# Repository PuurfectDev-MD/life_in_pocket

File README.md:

# Life in Pocket

This is a self-claimed cutesy 😛, portable, all-in-one journalling device for you to keep track of your life moments and memories through images taken through the inbuilt camera and voice recording taken through the inbuilt microphone. You can save memories with a title, detailed description and multiple pictures to enrich your journal timeline thorugh the means of an api to the website [Keep](https://keeplife.vercel.app/).

Create an account at [Keep](https://keeplife.vercel.app/) and begin Keep-ing :)

---

# Why build life_in_pocket?
I have always feared that life will just slip by while I am on autopilot. To tackle that fear I have always been keen on journalling and capturing moments to reminisce later. Building Keep and life_in_pocket has allowed me to do exactly that, capture life! I built this in the hopes of solving that fear/FOMO for me and potentially for others. 

---

## Custom build 3d Case

## Single board 2 layer PCB

# Features

**Capture Moments** — With the ondevice camera take pcitures and videos and save to sd card or/and upload to your keep account.

**Record Voice** — Record and reflect on your day, feelings and mood from the ondevice inp441 mic module to save to SD card or your Keep account.

**GUI on the TFT** — 2inch bright color tft screen where you can fetch your timeline straight from your keep account to view it ondevice without any phone or computer.

 See [Keep](https://github.com/PuurfectDev-MD/keep) for more details on the API and account.

---

# Project Structure
### 3D Case Assets
| Path / File | Description | Notes |
| :--- | :--- | :--- |
| **[3D Models](./3d%20models/)** | Root directory for all CAD data | — |
| `↳ /Fusion 360` | Original source files for the case design | — |
| `  ↳ assembly.f3d` | Master file with front/backplates & holes | **Use for printing** |
| `  ↳ frontplate.f3d` | Individual front component | Import file |
| `  ↳ backplate.f3d` | Individual back component | Import file |
| `  ↳ STEP files` | Standardized CAD format | Interoperability |
| `  ↳ STL files` | 3D printable mesh files | Slicer ready |
| `↳ /Kicad export` | 3D PCB model exported from KiCad | For mechanical fit |

### ⚡ PCB Assets
| Path / File | Description |
| :--- | :--- |
| **[PCB](./PCB/)** | Root directory for electronics |
| `↳ /Gerber file` | Contains `.zip` archive ready for manufacturing |
| `↳ /Kicad` | Full KiCad project source files |

###  Documentation & BOM
| File | Description | Format |
| :--- | :--- | :--- |
| **[BOM](./BOM/)** | Bill of Materials directory | Folder |
| `↳ BOM.pdf` | Comprehensive breakdown of project cost | [View PDF](./BOM/BOM%20.pdf) |
| `↳ BOM.csv` | BOM converted for spreadsheet use | [View CSV](./BOM/BOM.csv) |
| `↳ life_in_pocket.csv` | Technical BOM generated directly from KiCad | [View CSV](./BOM/life_in_pocket.csv) |
| **[Components.xlsx](./Components.xlsx)** | SMD vs. Hand-Solder tables (JLCPCB optimized) | Excel |
| **[Journal.md](./life-in-pocket-journal.md)** | Complete development log (Updated: May 10, 2025) | Markdown |

### Software & Media
| Category | Path / File | Description |
| :--- | :--- | :--- |
| **Software** | **[Firmware](./firmware/)** | Libraries and program files for ESP32-S3 |
| **Media** | **[Images](./images/)** | Assets and screenshots used in README |
| **Media** | **[`zine.png`](./zine.png)** | Project poster created for Fallout |
---

# How it works and how to make your own

There is a custom built PCB designed in KiCad where you solder the necessary components, then upload the firmware. To get it working you need to set your WiFi credentials and paste your Keep API key into the firmware.

Change the WiFi credentials in [setup.py](firmware/setup.py)and paste your API key from your Keep account in [actions.py](firmware/actions.py). Then 3D print the case using the files provided in the 3d models folder.

**Firmware** — setup.py initialises all the communication protocols, components and WiFi connection. From there, main.py listens for control changes and switches the active page accordingly, which then handles input differently depending on what page you are on.

**Hardware** — the components come together to create a polished physical experience. The TFT display handles the UI, the camera captures images, the mic module handles sound input and a speaker handles sound output. There are 4 inputs total, 2 capacitive TTP223 touch sensors and 2 MX switches. You capture memories through the camera and record voice memos through the mic, then hit upload and actions.py takes care of sending everything to your Keep account through the API.

The firmware is not 100% complete yet. Once I get all the components in hand, I will be testing the existing code, fixing issues and adding features along the way.

# Contributing

Feel free to reach out with suggestions or improvements on the pcb, 3d case or the website. I would be happy to work with anyone who wants to contribute to the project!

---

*Made with love ❤️*

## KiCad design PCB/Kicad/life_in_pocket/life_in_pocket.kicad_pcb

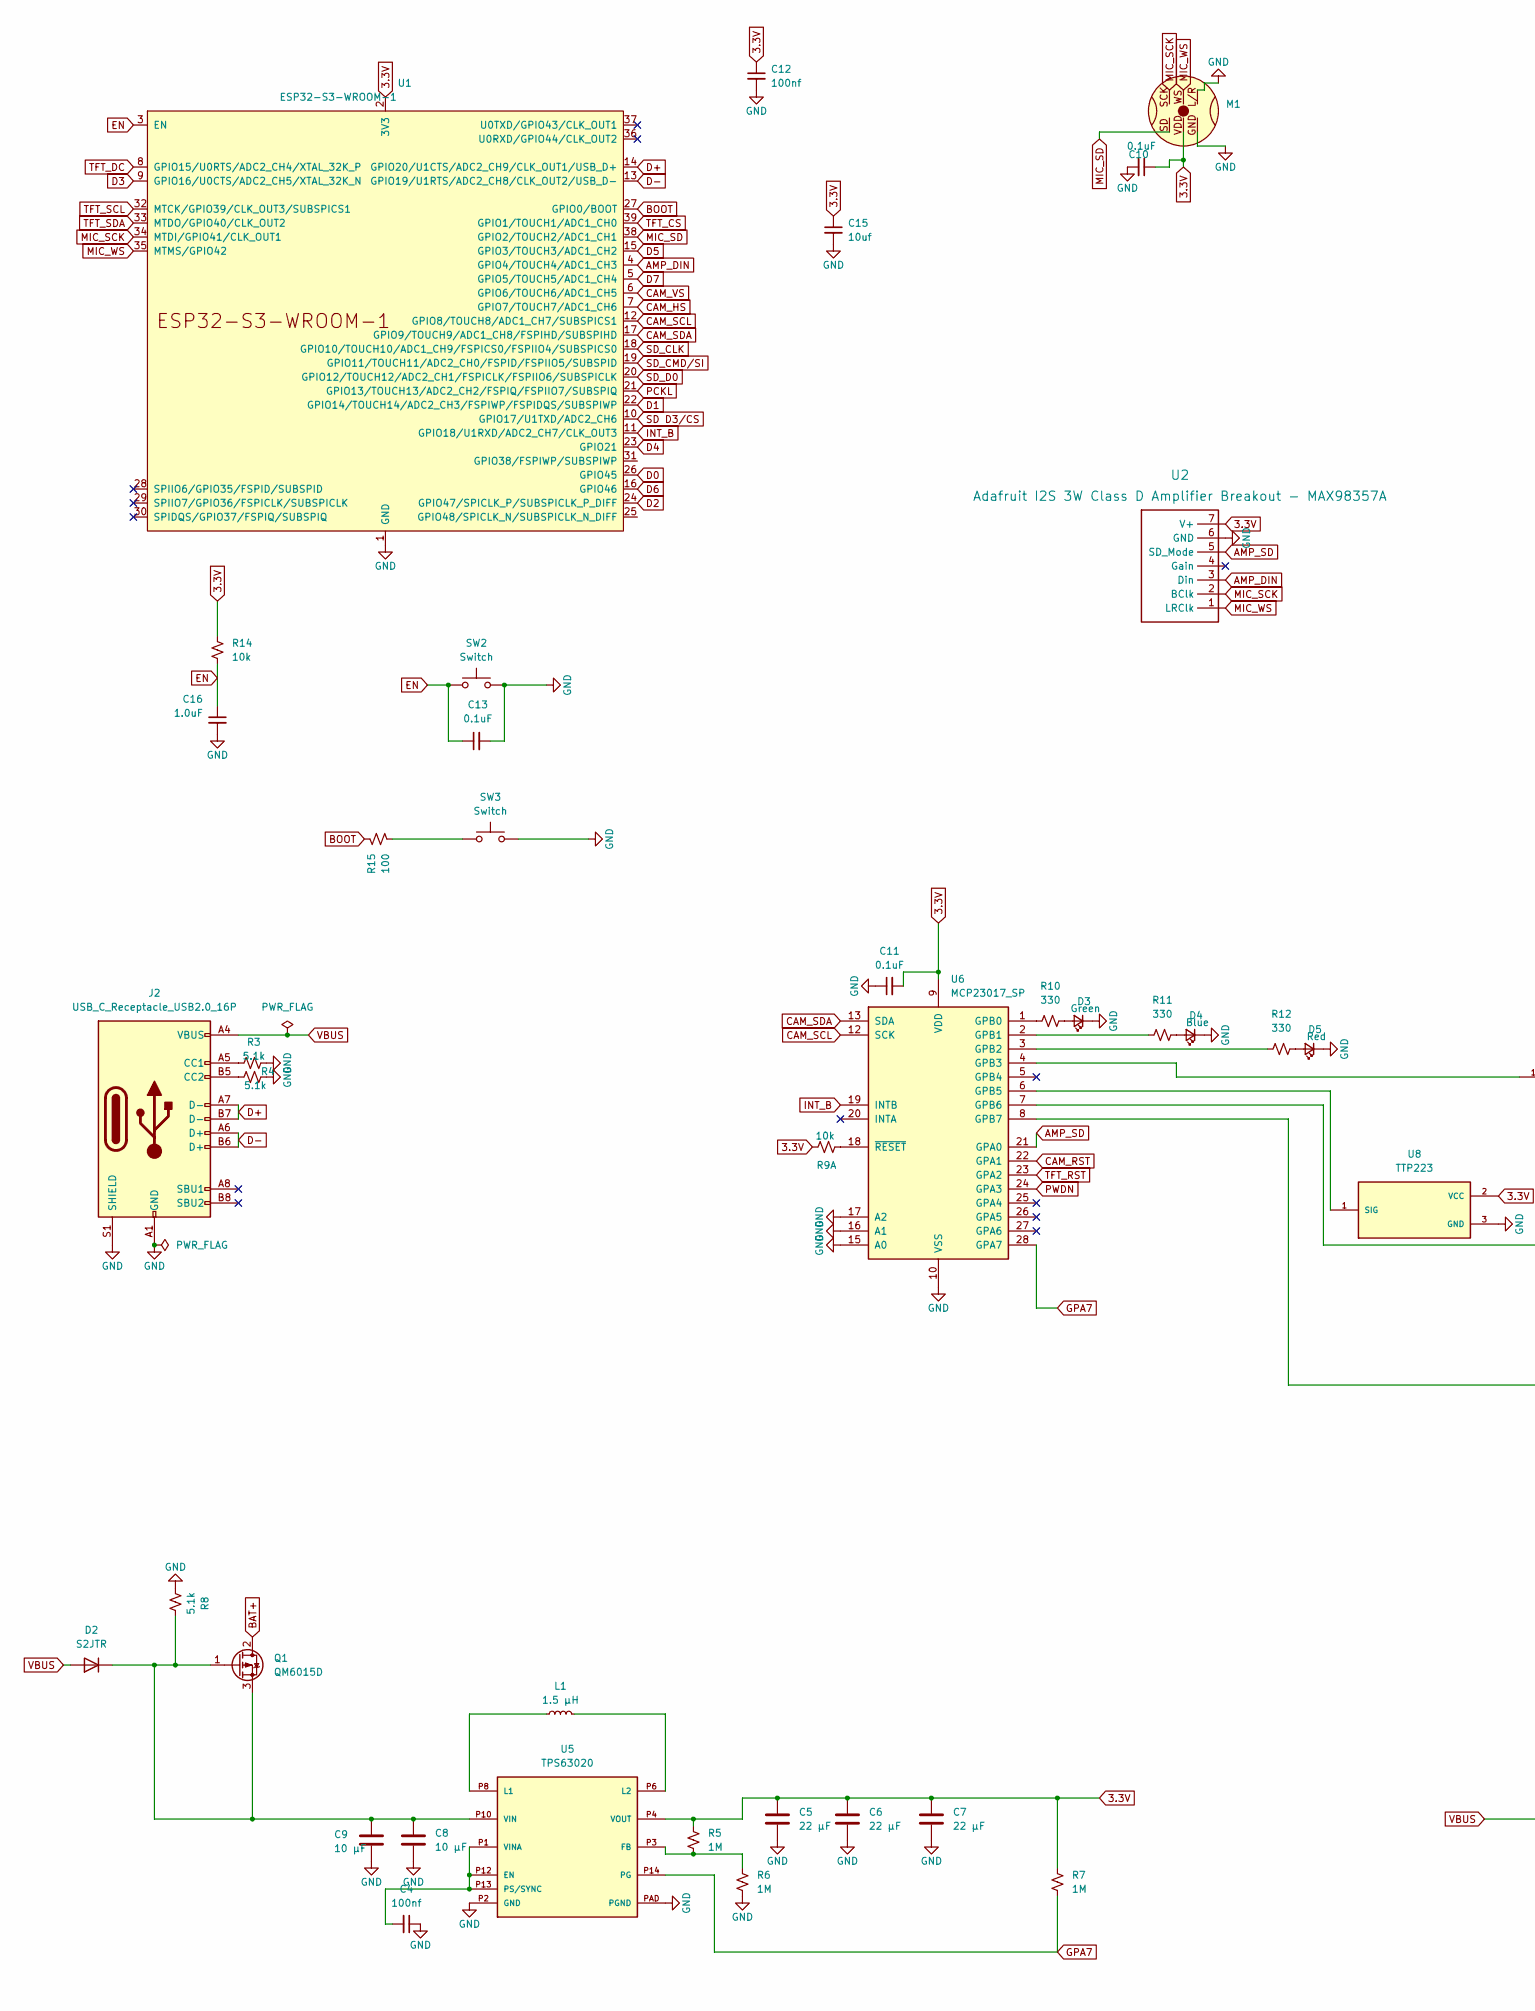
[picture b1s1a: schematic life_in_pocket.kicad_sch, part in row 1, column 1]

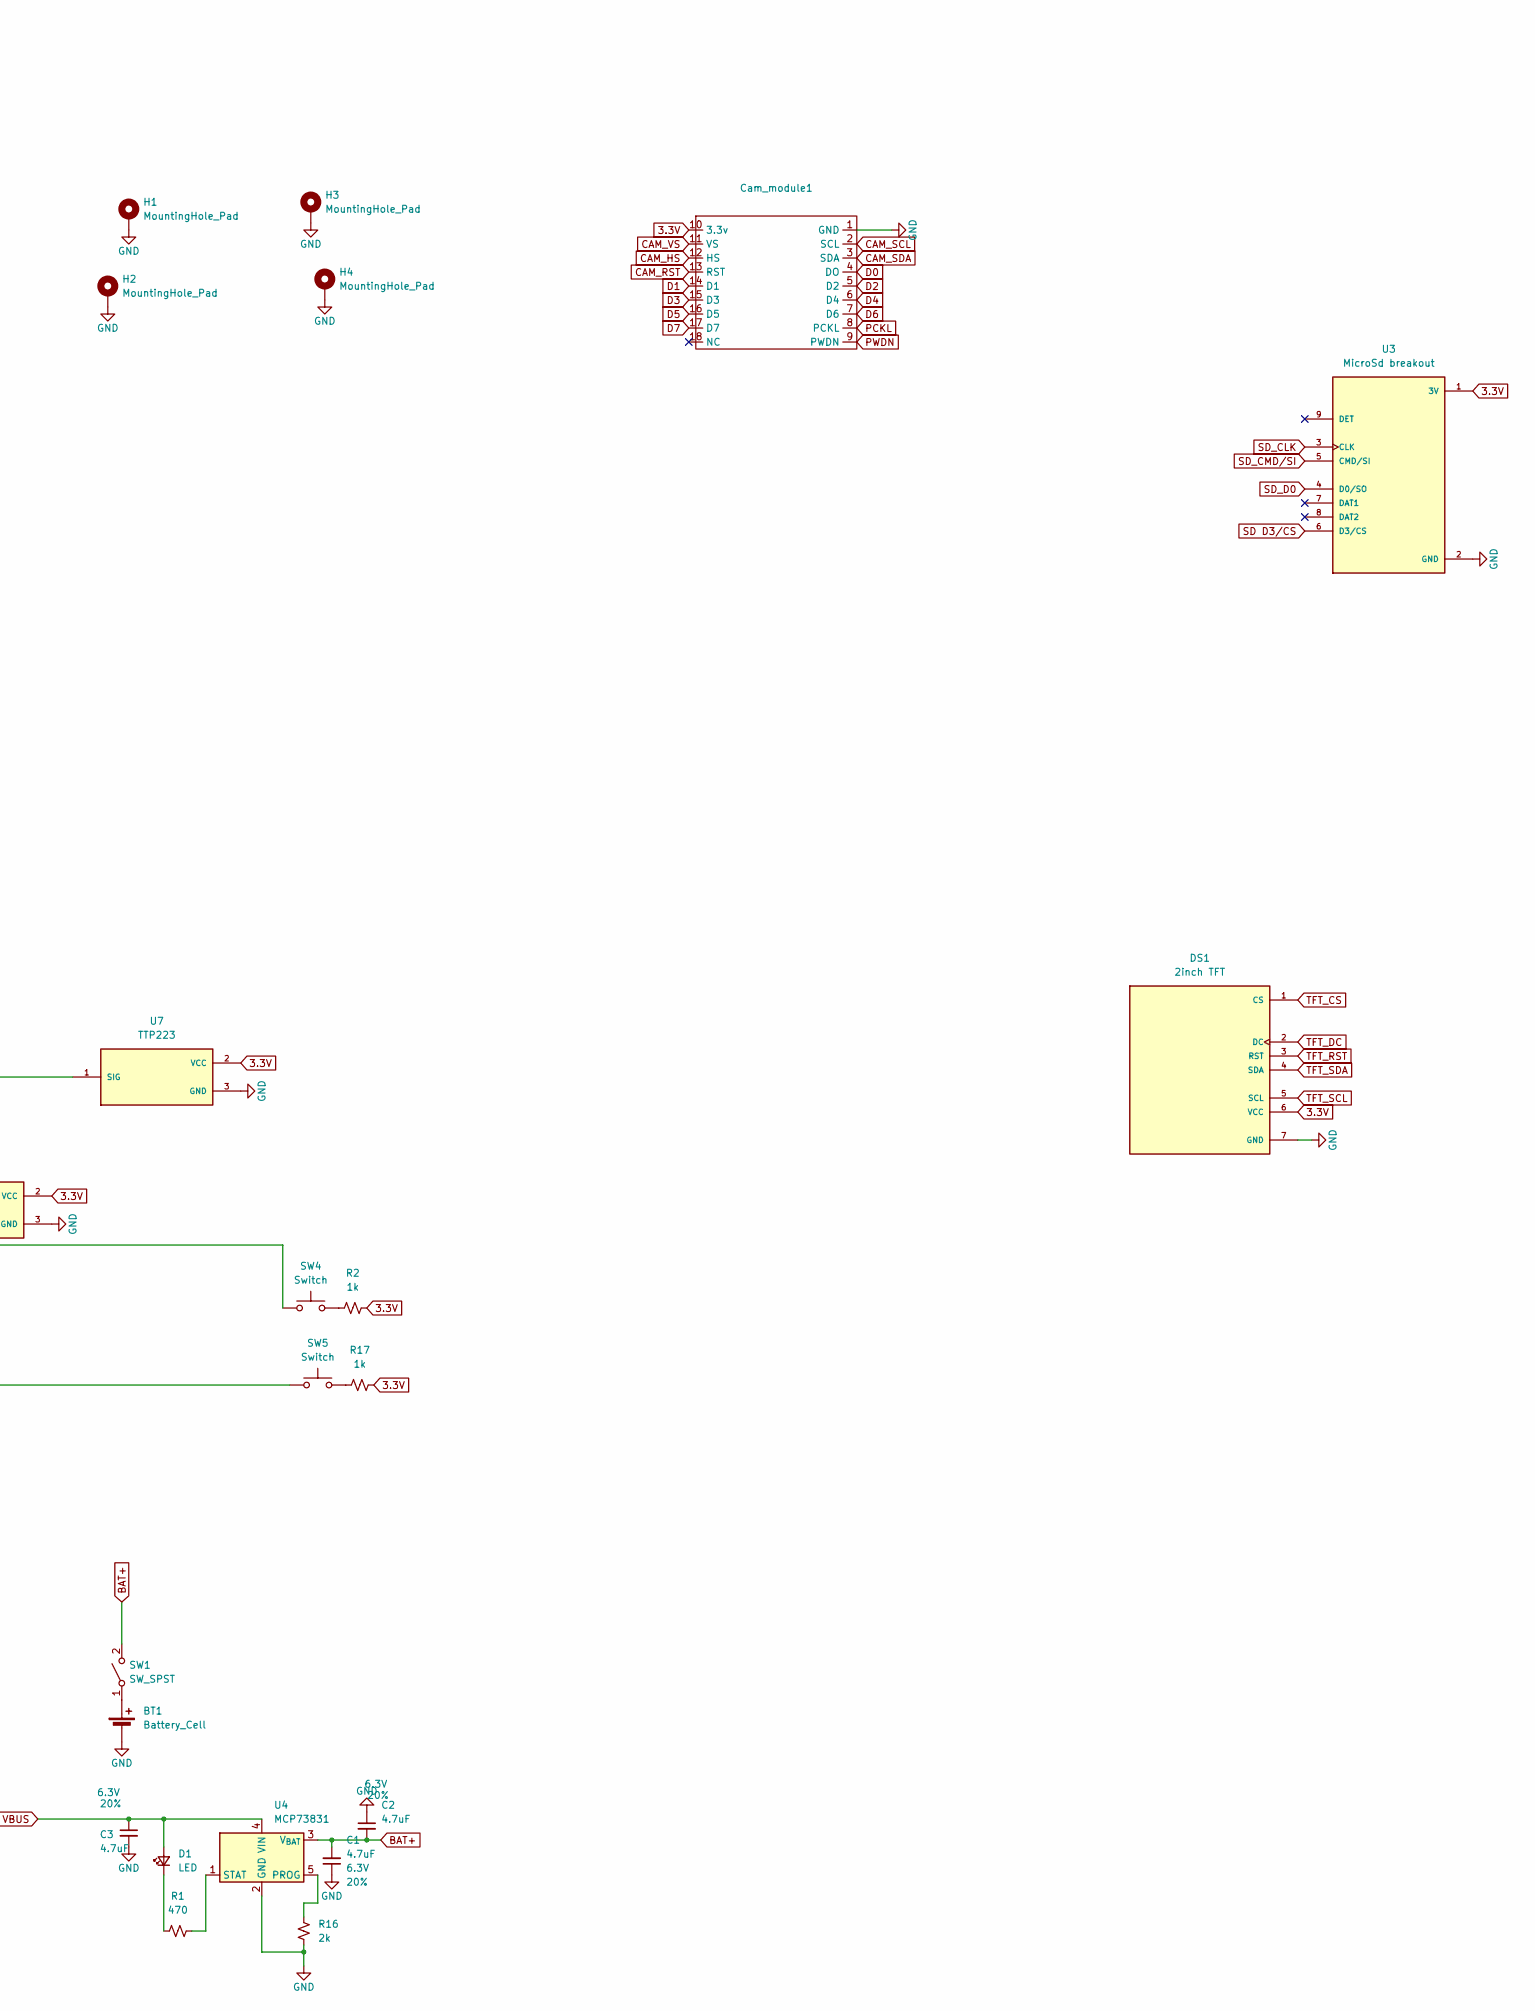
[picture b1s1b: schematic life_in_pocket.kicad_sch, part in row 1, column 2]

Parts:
BT1: Battery_Cell; JST_PH_B2B-PH-K_1x02_P2.00mm_Vertical
C1, C2, C3: 4.7uF; C_0603_1608Metric; Voltage 6.3V; Tolerance 20%
C4: 100nf; C_0603_1608Metric; Voltage 16V; Tolerance 10%
C5, C6, C7: 22 µF; C_0603_1608Metric
C8, C9: 10 µF; C_0603_1608Metric
C10, C11, C13: 0.1uF; C_0603_1608Metric; Voltage 16V; Tolerance 10%
C12: 100nf; C_0603_1608Metric; Voltage 1kV; Tolerance 100%
C15: 10uf; C_0603_1608Metric; Voltage 1kV; Tolerance 100%
C16: 1.0uF; C_0603_1608Metric; Voltage 16V; Tolerance 10%
Cam_module1: PinHeader_2x09_P2.54mm_Vertical
D1: LED; LED_0603_1608Metric
D2: S2JTR; D_0603_1608Metric
D3: Green; LED_0603_1608Metric
D4: Blue; LED_0603_1608Metric
D5: Red; LED_0603_1608Metric
DS1: 2inch TFT; MODULE_4311; PARTREV 2023-07-05; DigiKey_Part_Number 1528-4311-ND
H1, H2, H3, H4: MountingHole_Pad; MountingHole_3.2mm_M3
J2: USB_C_Receptacle_USB2.0_16P; USB_C_Receptacle_GCT_USB4105-xx-A_16P_TopMnt_Horizontal
L1: 1.5 µH; L_0603_1608Metric
M1: INMP441_module
Q1: QM6015D; TO-252-2
R1: 470; R_0603_1608Metric
R2, R17: 1k; R_0603_1608Metric
R3, R4, R8: 5.1k; R_0603_1608Metric
R5, R6, R7: 1M; R_0603_1608Metric
R9, R14: 10k; R_0603_1608Metric
R10, R11, R12: 330; R_0603_1608Metric
R15: 100; R_0603_1608Metric
R16: 2k; R_0603_1608Metric
SW1: SW_SPST; SolderWire-1sqmm_1x02_P7.8mm_D1.4mm_OD3.9mm
SW2, SW3: Switch; SW_Push_1P1T_NO_CK_KSC6xxG
SW4, SW5: Switch; MX_PCB_1.00u
U1: ESP32-S3-WROOM-1
U2: Adafruit I2S 3W Class D Amplifier Breakout - MAX9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; MAX98357A_Adafruit_Breakout; Manufacturer Part 3006
U3: MicroSd breakout; MODULE_MICROSD_SPI_OR_SDIO_CARD; PARTREV B
U4: MCP73831; SOT23-5
U5: TPS63020; QFN14_1
U6: MCP23017_SP; DIP-28_W7.62mm
U7, U8: TTP223; MODULE_ZC440600; PARTREV N/A

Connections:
3.3V: C5.1, C6.1, C7.1, C10.1, C11.2, C12.1, C15.1, Cam_module1.10 (3.3v), DS1.6 (VCC), M1.VDD, R2.2, R5.2, R7.2, R9.1, R14.2, R17.2, U1.2 (3V3), U2.7 (V+), U3.1 (3V), U5.P4 (VOUT), U5.P5 (VOUT), U6.9 (VDD), U7.2 (VCC), U8.2 (VCC); also elsewhere on the board
AMP_DIN: U1.4 (GPIO4/TOUCH4/ADC1_CH3), U2.3 (Din)
AMP_SD: U2.5 (SD_Mode), U6.21 (GPA0)
BAT+: C1.2, C2.2, Q1.2 (D), SW1.2 (B), U4.3 (V_{BAT})
BOOT: R15.2, U1.27 (GPIO0/BOOT)
CAM_HS: Cam_module1.12 (HS), U1.7 (GPIO7/TOUCH7/ADC1_CH6)
CAM_RST: Cam_module1.13 (RST), U6.22 (GPA1)
CAM_SCL: Cam_module1.2 (SCL), U1.12 (GPIO8/TOUCH8/ADC1_CH7/SUBSPICS1), U6.12 (SCK)
CAM_SDA: Cam_module1.3 (SDA), U1.17 (GPIO9/TOUCH9/ADC1_CH8/FSPIHD/SUBSPIHD), U6.13 (SDA)
CAM_VS: Cam_module1.11 (VS), U1.6 (GPIO6/TOUCH6/ADC1_CH5)
D0: Cam_module1.4 (DO), U1.26 (GPIO45), U1.31 (GPIO38/FSPIWP/SUBSPIWP)
D1: Cam_module1.14 (D1), U1.22 (GPIO14/TOUCH14/ADC2_CH3/FSPIWP/FSPIDQS/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)
D2: Cam_module1.5 (D2), U1.24 (GPIO47/SPICLK_P/SUBSPICLK_P_DIFF)
D3: Cam_module1.15 (D3), U1.9 (GPIO16/U0CTS/ADC2_CH5/XTAL_32K_N)
D4: Cam_module1.6 (D4), U1.23 (GPIO21)
D5: Cam_module1.16 (D5), U1.15 (GPIO3/TOUCH3/ADC1_CH2); also elsewhere on the board
D6: Cam_module1.7 (D6), U1.16 (GPIO46), U1.25 (GPIO48/SPICLK_N/SUBSPICLK_N_DIFF)
D7: Cam_module1.17 (D7), U1.5 (GPIO5/TOUCH5/ADC1_CH4)
D+: J2.A7 (D-), J2.B7 (D-), U1.14 (GPIO20/U1CTS/ADC2_CH9/CLK_OUT1/USB_D+)
D-: J2.A6 (D+), J2.B6 (D+), U1.13 (GPIO19/U1RTS/ADC2_CH8/CLK_OUT2/USB_D-)
EN: C13.1, C16.1, R14.1, SW2.1, U1.3 (EN)
GND: BT1.2 (-), C1.1, C2.1, C3.2, C4.1, C5.2, C6.2, C7.2, C8.2, C9.2, C10.2, C11.1, C12.2, C13.2, C15.2, C16.2, Cam_module1.1 (GND), D3.1 (K), D4.1 (K), D5.1 (K), DS1.7 (GND), H1.1 (1_1), H2.1 (1_1), H3.1 (1_1), H4.1 (1_1), J2.A1 (GND), J2.A12 (GND), J2.B1 (GND), J2.B12 (GND), J2.S1 (SHIELD), M1.GND, M1.L/R, R3.2, R4.2, R6.1, R8.1, R16.1, SW2.2, SW3.2, U1.1 (GND), U1.40 (GND), U1.41 (GND), U2.6 (GND), U3.2 (GND), U4.2 (GND), U5.P2 (GND), U5.PAD (PGND), U6.10 (VSS), U6.15 (A0), U6.16 (A1), U6.17 (A2), U7.3 (GND), U8.3 (GND)
GPA7: R7.1, U5.P14 (PG), U6.28 (GPA7)
INT_B: U1.11 (GPIO18/U1RXD/ADC2_CH7/CLK_OUT3), U6.19 (INTB)
MIC_SCK: M1.SCK, U1.34 (MTDI/GPIO41/CLK_OUT1), U2.2 (BClk)
MIC_SD: M1.SD, U1.38 (GPIO2/TOUCH2/ADC1_CH1)
MIC_WS: M1.WS, U1.35 (MTMS/GPIO42), U2.1 (LRClk)
unnamed: BT1.1 (+), SW1.1 (A)
unnamed: D1.1 (K), R1.2
unnamed: C8.1, C9.1, D2.1 (K), Q1.1 (G), Q1.3 (S), R8.2, U5.P10 (VIN), U5.P11 (VIN)
unnamed: D3.2 (A), R10.2
unnamed: D4.2 (A), R11.2
unnamed: D5.2 (A), R12.2
unnamed: J2.A5 (CC1), R3.1
unnamed: J2.B5 (CC2), R4.1
unnamed: L1.1, U5.P8 (L1), U5.P9 (L1)
unnamed: L1.2, U5.P6 (L2), U5.P7 (L2)
unnamed: R2.1, SW4.2
unnamed: R15.1, SW3.1
unnamed: R17.1, SW5.2
unnamed: R16.2, U4.5 (PROG)
unnamed: R1.1, U4.1 (STAT)
unnamed: C4.2, U5.P1 (VINA), U5.P12 (EN), U5.P13 (PS/SYNC)
unnamed: R5.1, R6.2, U5.P3 (FB)
unnamed: R10.1, U6.1 (GPB0)
unnamed: R11.1, U6.2 (GPB1)
unnamed: R12.1, U6.3 (GPB2)
unnamed: U6.4 (GPB3), U7.1 (SIG)
unnamed: U6.6 (GPB5), U8.1 (SIG)
unnamed: SW4.1, U6.7 (GPB6)
unnamed: SW5.1, U6.8 (GPB7)
unnamed: R9.2, U6.18 (~RESET)
PCKL: Cam_module1.8 (PCKL), U1.21 (GPIO13/TOUCH13/ADC2_CH2/FSPIQ/FSPIIO7/S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)
PWDN: Cam_module1.9 (PWDN), U6.24 (GPA3); also elsewhere on the board
SD D3/CS: U1.10 (GPIO17/U1TXD/ADC2_CH6), U3.6 (D3/CS)
SD_CLK: U1.18 (GPIO10/TOUCH10/ADC1_CH9/FSPICS0/FSPIIO4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), U3.3 (CLK)
SD_CMD/SI: U1.19 (GPIO11/TOUCH11/ADC2_CH0/FSPID/FSPIIO5/S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), U3.5 (CMD/SI)
SD_D0: U1.20 (GPIO12/TOUCH12/ADC2_CH1/FSPICLK/FSPIIO6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), U3.4 (D0/SO)
TFT_CS: DS1.1 (CS), U1.39 (GPIO1/TOUCH1/ADC1_CH0)
TFT_DC: DS1.2 (DC), U1.8 (GPIO15/U0RTS/ADC2_CH4/XTAL_32K_P)
TFT_RST: DS1.3 (RST), U6.23 (GPA2)
TFT_SCL: DS1.5 (SCL), U1.32 (MTCK/GPIO39/CLK_OUT3/SUBSPICS1)
TFT_SDA: DS1.4 (SDA), U1.33 (MTDO/GPIO40/CLK_OUT2)
VBUS: C3.1, D1.2 (A), D2.2 (A), J2.A4 (VBUS), J2.A9 (VBUS), J2.B4 (VBUS), J2.B9 (VBUS), U4.4 (VIN)

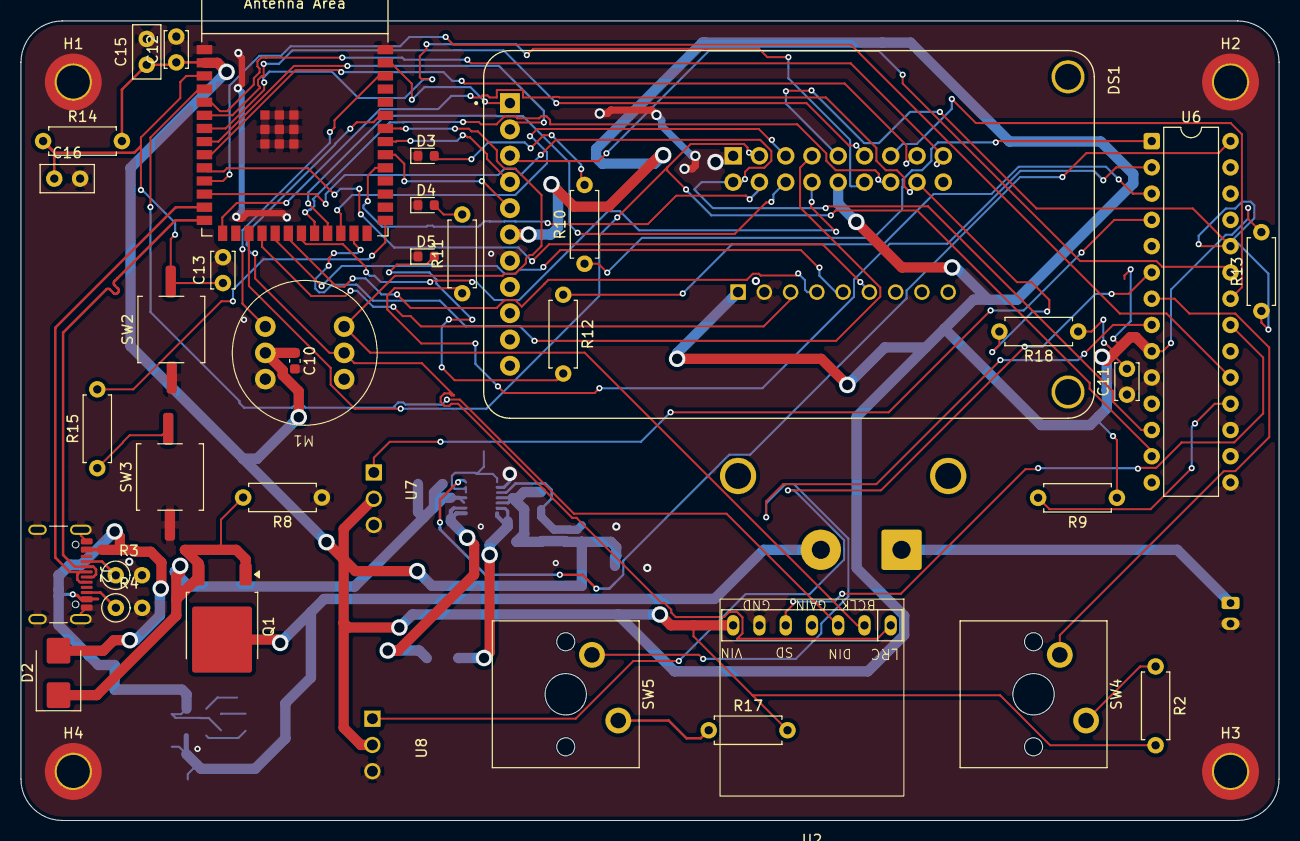
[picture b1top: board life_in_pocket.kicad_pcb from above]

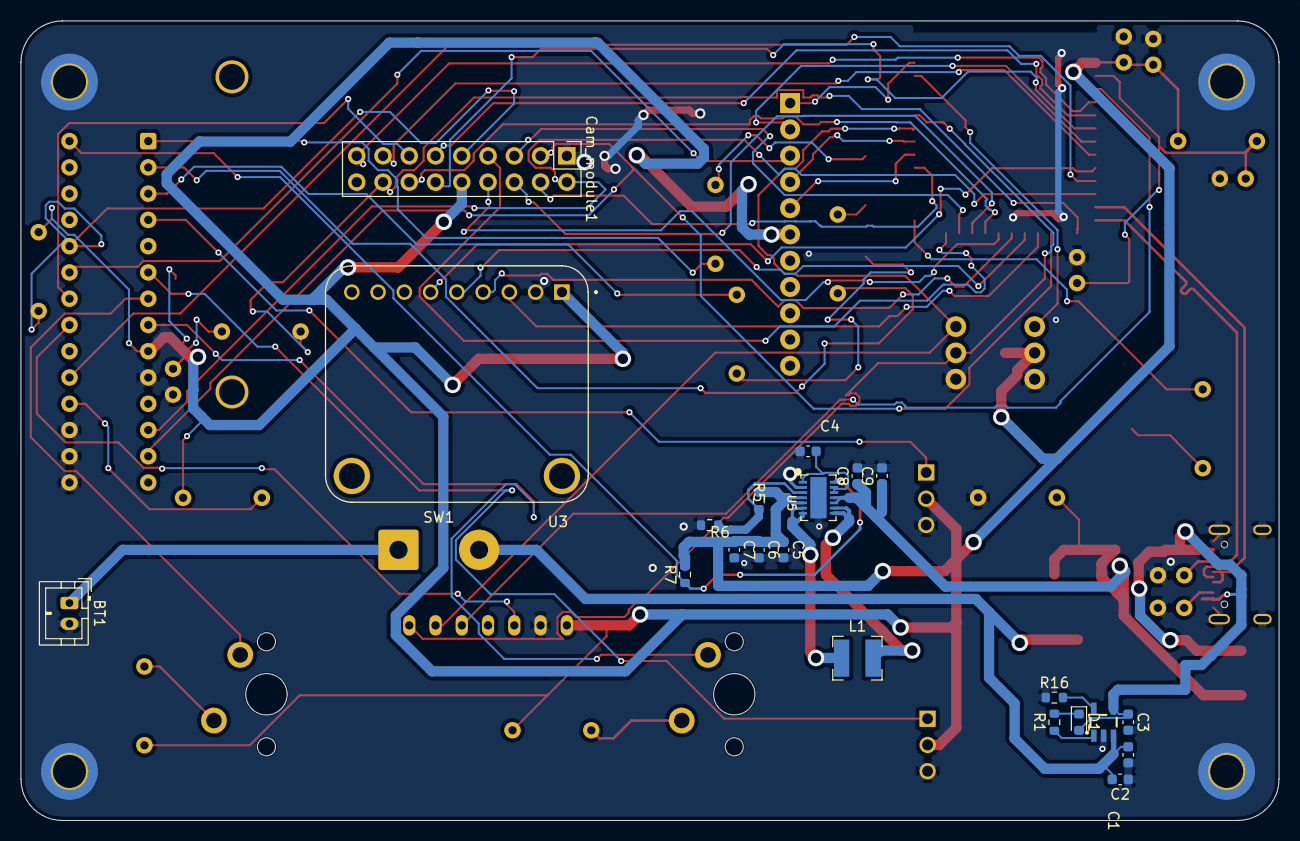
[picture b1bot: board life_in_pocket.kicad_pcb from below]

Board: 2 copper layers, 121.7 x 77.3 mm, 62 parts (22 on the bottom side), 64 nets.

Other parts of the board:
R13, R18: 10k; R_Axial_DIN0207_L6.3mm_D2.5mm_P7.62mm_Horizontal

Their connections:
3.3V: R13.2, R18.1; also elsewhere on the board
D5: R18.2; also elsewhere on the board
PWDN: R13.1; also elsewhere on the board

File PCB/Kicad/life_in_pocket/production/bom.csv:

Designator,Footprint,Quantity,Value,LCSC Part #
BT1,JST_PH_B2B-PH-K_1x02_P2.00mm_Vertical,1,Battery_Cell,
"C1, C2, C3",0603,3,4.7uF,
"C10, C11, C13",0603,3,0.1uF,
"C12, C4",0603,2,100nf,
C15,0603,1,10uf,
C16,0603,1,1.0uF,
"C5, C6, C7",0603,3,22 µF,
"C8, C9",0603,2,10 µF,
CAM_MODULE1,PinHeader_2x09_P2.54mm_Vertical,1,~,
D1,0603,1,LED,
D2,0603,1,S2JTR,
D3,0603,1,Green,
D4,0603,1,Blue,
D5,0603,1,Red,
DS1,MODULE_4311,1,2inch TFT,
J2,USB_C_Receptacle_GCT_USB4105-xx-A_16P_TopMnt_Horizontal,1,USB_C_Receptacle_USB2.0_16P,
L1,0603,1,1.5 µH,
M1,INMP441_module,1,~,
Q1,TO-252-2,1,QM6015D,
R1,0603,1,470,
"R10, R11, R12",0603,3,330,
"R13, R14, R18, R9",0603,4,10k,
R15,0603,1,100,
R16,0603,1,2k,
"R17, R2",0603,2,1k,
"R3, R4, R8",0603,3,5.1k,
"R5, R6, R7",0603,3,1M,
SW1,SolderWire-1sqmm_1x02_P7.8mm_D1.4mm_OD3.9mm,1,SW_SPST,
"SW2, SW3",SW_Push_1P1T_NO_CK_KSC6xxG,2,Switch,
"SW4, SW5",MX_PCB_1.00u,2,Switch,
U1,ESP32-S3-WROOM-1,1,ESP32-S3-WROOM-1,
U2,MAX98357A_Adafruit_Breakout,1,Adafruit I2S 3W Class D Amplifier Breakout - MAX98357A,
U3,MODULE_MICROSD_SPI_OR_SDIO_CARD,1,MicroSd breakout,
U4,SOT23-5,1,MCP73831,
U5,QFN14_1,1,TPS63020,
U6,DIP-28_W7.62mm,1,MCP23017_SP,
"U7, U8",MODULE_ZC440600,2,TTP223,

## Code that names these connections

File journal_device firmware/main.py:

import machine
import setup
import asyncio
import ui
from setup import defineAllComp
import time

TFT_SDA = 40
TFT_SCL =39
TFT_CS = 1
TFT_DC =15

SD_D0 =12 #spi miso pin
SD_CMD =11 #spi mosi
SD_CLK= 10#clck signal
SD_D3 =17 #spi cs pin

CAM_SDA= 9
CAM_SCL =8


INT_B = 18

class Device:
    def __init__(self):
        setup = defineAllComp()
        
        self.spi_tft = setup.defineSPI(id=1,baudrate=4000000, SCK=TFT_SCL,MOSI=TFT_SDA, MISO=None)
        self.spi_sd = setup.defineSPI(id=2,baudrate=2000000, SCK=SD_CLK,MOSI=SD_CMD, MISO=SD_D0)
        self.mcp = setup.defineExpander(scl_pin=8, sda_pin=9)
        
        self.btn_state = False
        self.int_pin = machine.Pin(19, machine.Pin.IN, machine.Pin.PULL_UP) # Check if it's 18 or 19
        self.int_pin.irq(trigger=machine.Pin.IRQ_FALLING, handler=self.isr)
        
        self.tft = setup.defineTFT(self.spi_tft, mcp=self.mcp, TFT_DC= TFT_DC,TFT_CS=TFT_CS, rotation=0)
        self.sd = setup.defineSdcard(self.spi_sd, CS=SD_D3)
        
        self.pages = {
            "home": ui.HomePage(self.tft, self),
            "camera": ui.CameraPage(self.tft, self)
        }
        
    def isr(self, pin):
        self.btn_state = True
        
        
    def get_ui_event(self):
        if not self.btn_state:
            return None
        
        # Read raw data from the setup tool
        raw = self.mcp.portb.intcap 
        self.btn_state = False # Clear the interrupt flag
        
        # Mapping logic stays here in the main app
        events = []
        if bool(raw & (1 << 4)): events.append("UP")
        if bool(raw & (1 << 6)): events.append("DOWN")
        if not bool(raw & (1 << 7)): events.append("LEFT")
        if not bool(raw & (1 << 8)): events.append("RIGHT")
        
        return events # e.g., ["LEFT", "UP"]
    
    
    

device = Device()
current_page = device.pages["home"]
current_page.draw()


while True:
    events = device.get_ui_event()
    
    if events:
        new_page_key = current_page.handle_input(events)
        if new_page_key and new_page_key in device.pages:
            current_page = device.pages[new_page_key]
            current_page.draw()
            
    time.sleep_ms(50)
                                        

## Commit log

2026-04-11 First push
2026-04-16 Finished rerouting- all critical errors resolved
2026-04-20 Kicad stuff done. began firmware setup
2026-05-01 Added actions
2026-05-02 README update
2026-05-02 BOM, POSTER and README update
2026-05-03 BOM and README update
2026-05-08 Updated zine
2026-05-10 Assembly file and bom.csv file
2026-05-10 Final README.md update
2026-06-17 Fixed camera data connections
2026-06-20 Changed pcb's components to THT (top side only) for cheaper assembly
